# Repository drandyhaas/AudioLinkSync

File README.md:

# AudioLinkSync
Code and design files etc for a small device that delays digital audio.

Audio comes in on Toslink Spdif digital fiber, gets converted to electrical by DLR1150, then processed (delayed)
by a Teensy 4.0, then converted back to optical by a DLT1150, and back out on fiber.

The Teensy runs Arduino code with an audio library that can delay the music by up to 750 ms, in 1 ms steps.

A button and knob are used to adjust the delay. Hold the button down a few seconds until the LED comes on - you can then adjust the delay using the knob. Then hold the button down a few seconds again until the LED goes off - the delay is then locked.

An ssd1360 screen shows the delay and stats in real time.

PCB:

Product:

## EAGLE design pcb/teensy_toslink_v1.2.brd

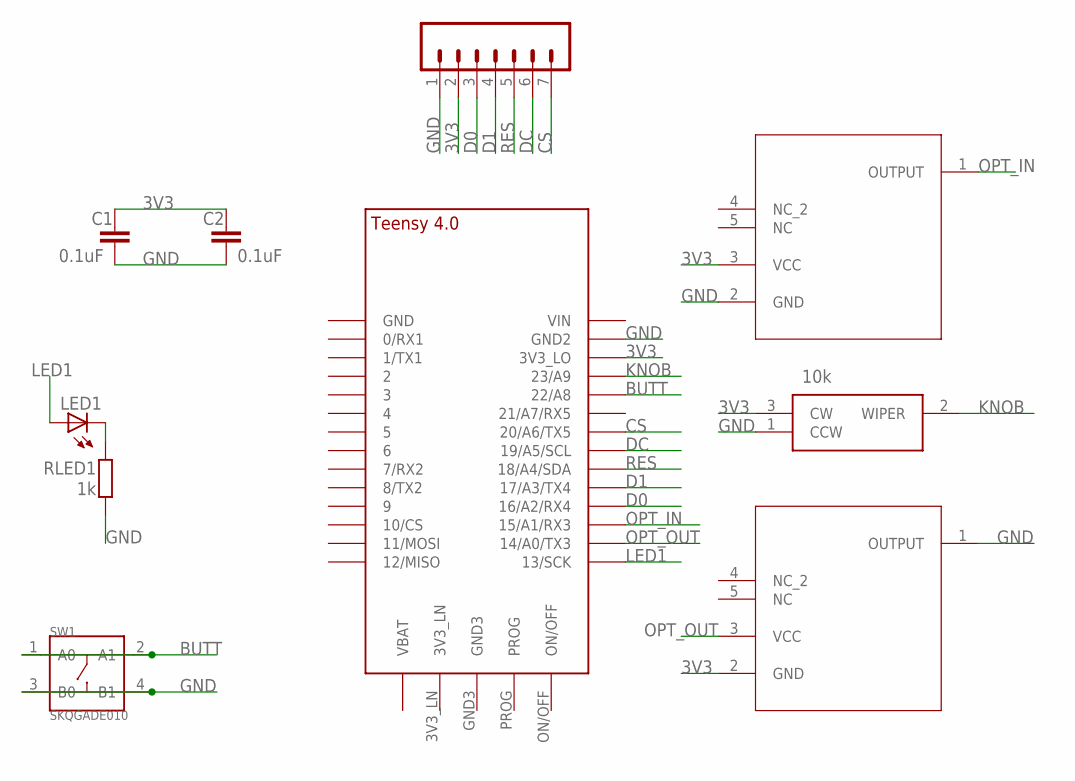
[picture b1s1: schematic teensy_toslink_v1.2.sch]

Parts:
C1, C2: 0.1uF; C0805
CN1: 8p-2.54; 1X07
J1, J2: TORX141P(F)TORX141P(F)_TOS; TORX141P(F)_TOS
LED1: 0805; CHIPLED_0805
RLED1: 1k; R0805
SW1: SKQGADE010; SW4-SMD-5.2X5.2X1.5MM
U$1: TEENSY_4.0
VR1: 10k; 3386P1103TLF

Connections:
3V3: C1.1, C2.1, CN1.2, J1.3 (VCC), J2.2 (GND), U$1.3V3_LO, VR1.3 (CW)
BUTT: SW1.1 (A0), SW1.2 (A1), U$1.22/A8
CS: CN1.7, U$1.20/A6 (20/A6/TX5)
D0: CN1.3, U$1.16/A2 (16/A2/RX4)
D1: CN1.4, U$1.17/A3 (17/A3/TX4)
DC: CN1.6, U$1.19/A5/SCL
GND: C1.2, C2.2, CN1.1, J1.2 (GND), J2.1 (OUTPUT), RLED1.1, SW1.3 (B0), SW1.4 (B1), U$1.GND2, VR1.1 (CCW)
KNOB: U$1.23/A9, VR1.2 (WIPER)
LED1: LED1.A, U$1.13/SCK
unnamed: LED1.C, RLED1.2
OPT_IN: J1.1 (OUTPUT), U$1.15/A1 (15/A1/RX3)
OPT_OUT: J2.3 (VCC), U$1.14/A0 (14/A0/TX3)
RES: CN1.5, U$1.18/A4/SDA

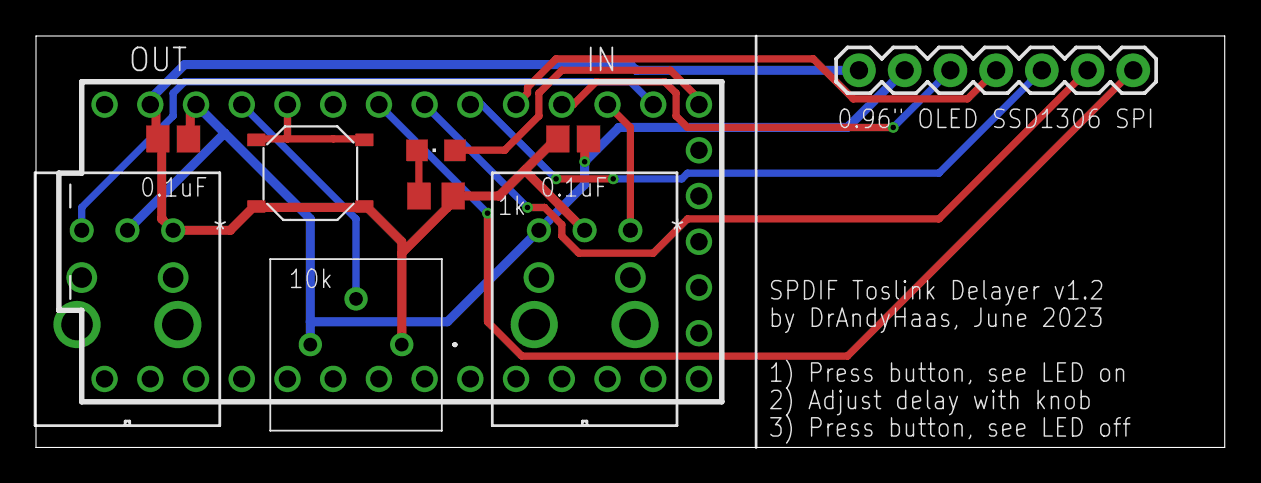
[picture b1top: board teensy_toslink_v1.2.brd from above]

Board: 2 copper layers, 66.0 x 22.9 mm, 10 parts (0 on the bottom side), 13 nets.

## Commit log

2023-06-29 initial commit, v1.1
2023-06-29 add peak volume, reduce CPU speed to 150 MHz
2023-07-05 final v1.1
2024-07-01 pic of pcb layout

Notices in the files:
parts and their libraries:
SparkFun-Connectors: Licensing: Creative Commons ShareAlike 4.0 International - https://creativecommons.org/licenses/by-sa/4.0
COPYRIGHT: Copyright (C) 2023 Ultra Librarian. All rights reserved.
